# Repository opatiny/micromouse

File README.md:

# Algernon: A custom micromouse robot

YouTube demo of the project: https://youtu.be/nz4QlaSIkbY

Main repository for my bachelor's thesis project.

## Related repositories

The software fo this robot can be found in the two following repositories:

- Software for the microcontroller: [opatiny/ms-software](https://github.com/opatiny/ms-software)
- TypeScript code for the debug web page (is then built and uploaded on the MCU): [opatiny/ms-webpage](https://github.com/opatiny/ms-webpage)

## Abstract

This project was inspired by the micromouse competitions, in which small autonomous maze-solving robots compete to solve an unknown maze in the shortest possible time. The main focus of the project was to design a micromouse from scratch, which implied electrical and mechanical design, as well as the manufacturing of our own custom PCB. A physical prototype of the robot was fully assembled and tested. The robot implements 5 ToF distance sensors, an accelerometer and two brushed DC motors with encoders. The microcontroller is an ESP32-S3, and a 2P1S LiPo battery is used as a power supply. On the software side, all of the sensors were tested independently and are functional. A basic odometry task was also implemented, which allows to track the robot's position, and speed regulation of the wheels was added. What is more, a remote debug interface using WiFi was programmed in order to visualize the robot's status in real time.

## Report of the project

The report of this thesis can be found in the `docs` folder of this repository: [bachelor-thesis-opatiny.pdf](./docs/bachelor-thesis-opatiny.pdf)

## Repository structure

These are the main folders in this repository:

- `docs`: All sorts of documentation about the project, as well as the datasheets and useful images of the components used.
- `electronics`: Contains all the KiCad files of the PCB.
- `mechanics`: All files related to mechanical design and manufacturing. Also contains all of our custom maze files.
- `matlab`: Calculations and plot realized during the project.
- `software`: Not the actual micro-controller software. This only contains a few tests done using the Micromouse Simulator tool.

## Software

All the software of the robot is in its own repository: [opatiny/ms-software](https://github.com/opatiny/micromouse).

## Electronic design

The robot's PCB was fully designed in KiCad. The list of all the components used can be found in [docs/electronics/mouseHardware.md](./docs/electronics/mouseHardware.md).

Render of the final PCB

3D view of the completed robot

## Mechanical design

The mechanical design is relatively simple since the PCB is the main structural element. We just had to design our own caster wheel, that are 3D printed out of PETG, and custom bumpers, 3D printed out of flexible filament.

Comparison of commercial and custom caster wheel

Close-up of the bumper

## Custom maze

In order to test our robot, we designed our own maze. The walls are 3mm MDF, spray painted white. The connectors are 3D printed out of PETG. Additional "bridge" parts are use to ensure the walls are parallel, and at the right distance from each other. All the parts were designed in solidworks.

The four types of connectors

Example of a small section of maze, integrating one of the "bridge" parts

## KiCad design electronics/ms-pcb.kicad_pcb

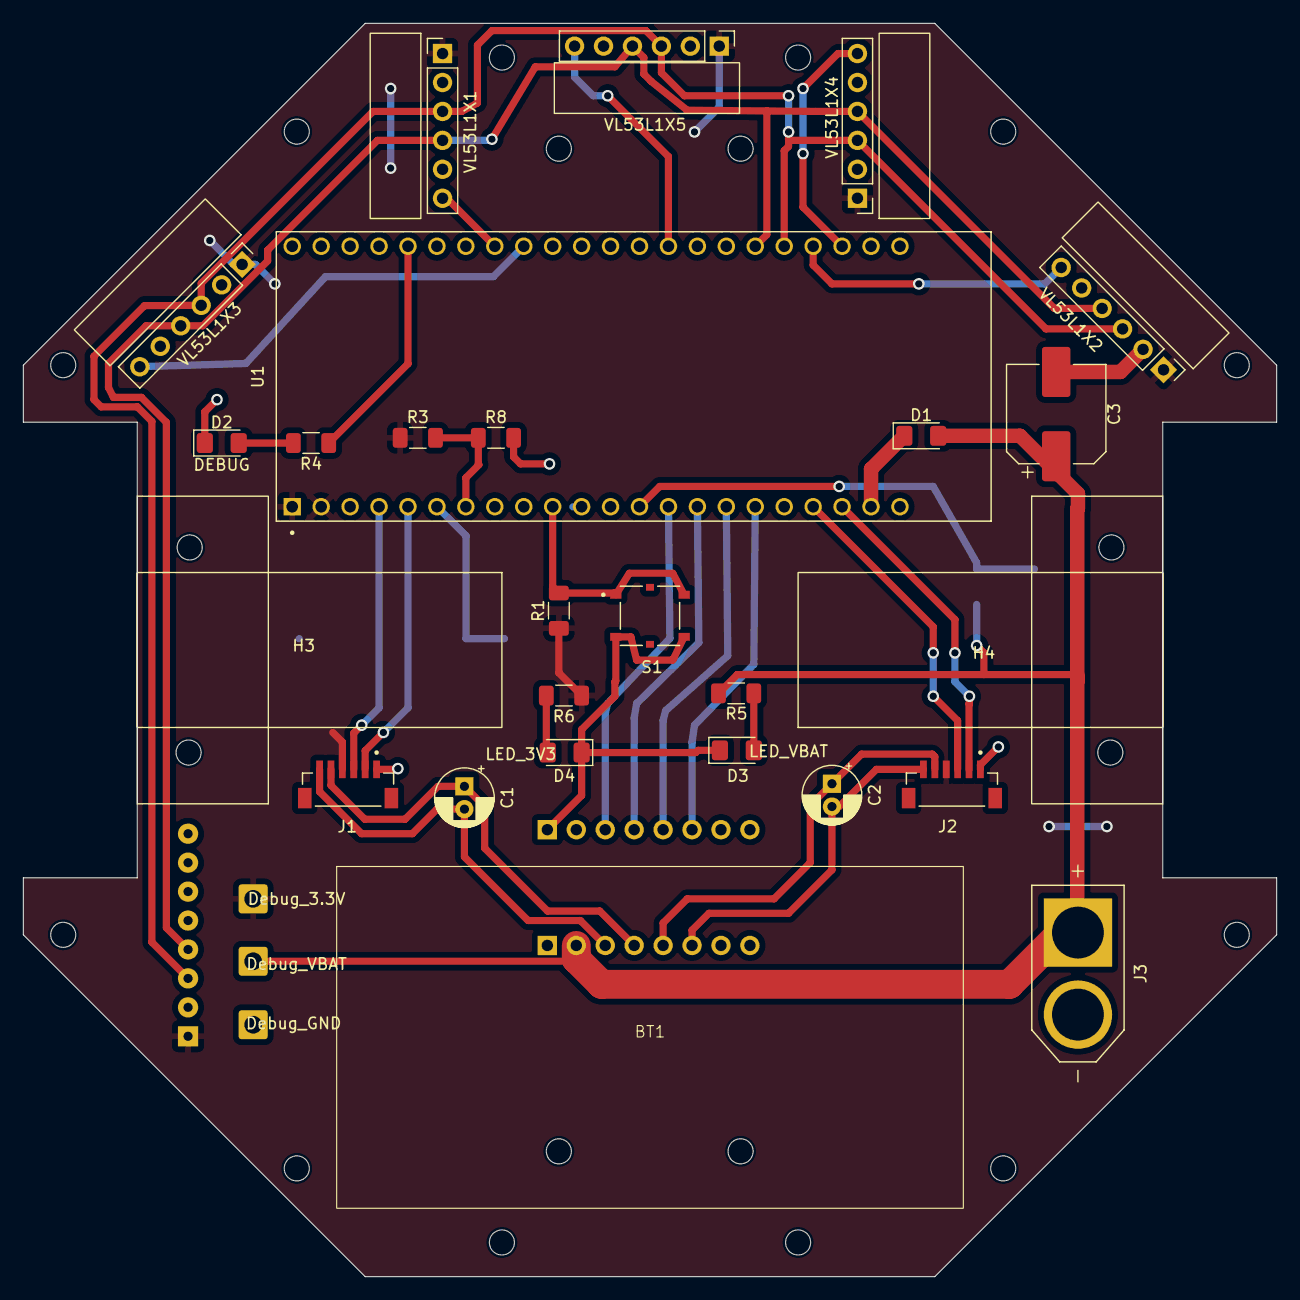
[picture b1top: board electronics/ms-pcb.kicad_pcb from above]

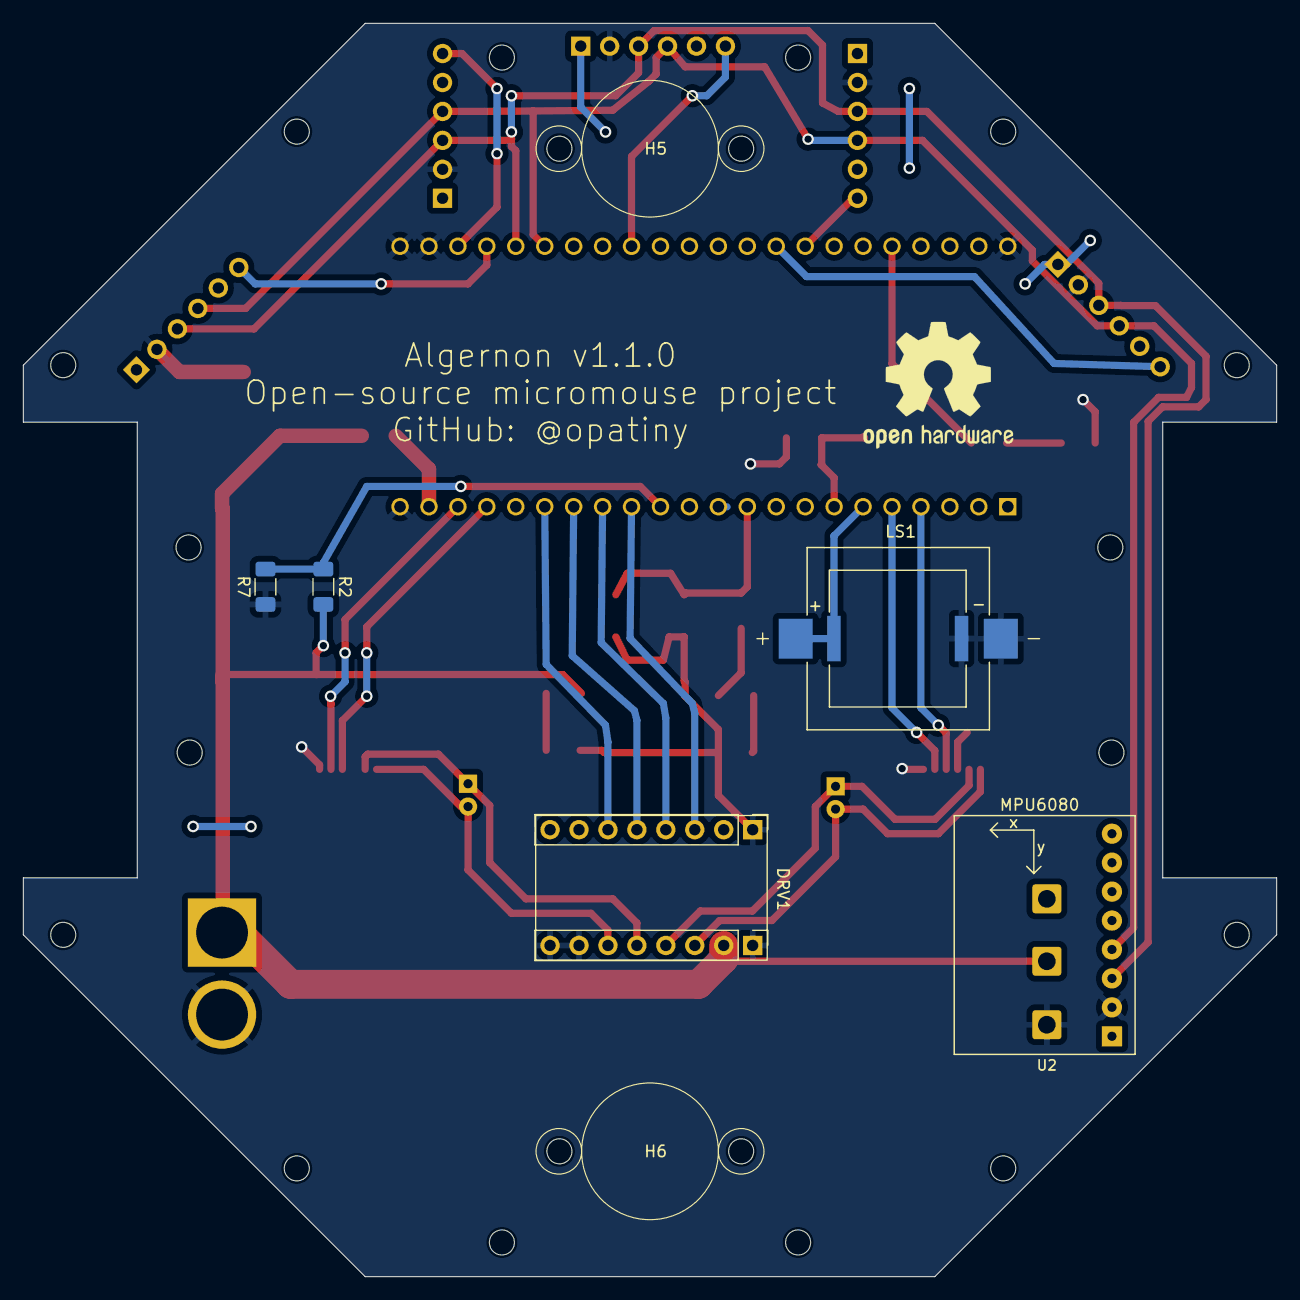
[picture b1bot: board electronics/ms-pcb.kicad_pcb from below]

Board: 2 copper layers, 110.0 x 110.0 mm, 38 parts (7 on the bottom side), 31 nets.

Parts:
BT1: Battery; LiPo_2S1P_Battery
C1, C2: 0.1uF; CP_Radial_D5.0mm_P2.00mm
C3: 220uF; CP_Elec_8x10.5
D1: D_Schottky; D_1206_3216Metric_Pad1.42x1.75mm_HandSolder
D2: DEBUG; LED_1206_3216Metric_Pad1.42x1.75mm_HandSolder
D3: LED_VBAT; LED_1206_3216Metric_Pad1.42x1.75mm_HandSolder
D4: LED_3V3; LED_1206_3216Metric_Pad1.42x1.75mm_HandSolder
DRV1: DRV8833; Polulu_DRV8833
H1: Bumper_front; Micromouse_bumper
H2: Bumper_back; Micromouse_bumper
H3, H4: Motor_holes; Polulu_Micro_Gearmotor
H5, H6: Caster_wheel; caster_wheel_custom
H7: Debug_3.3V; SolderWire-0.75sqmm_1x01_D1.25mm_OD2.3mm
H8: Debug_VBAT; SolderWire-0.75sqmm_1x01_D1.25mm_OD2.3mm
H9: Debug_GND; SolderWire-0.75sqmm_1x01_D1.25mm_OD2.3mm
J1: Left motor; JST_SH_6pins
J2: Right motor; JST_SH_6pins
J3: XT60-M; AMASS_XT60-M
LS1: PKLCS1212E20A0-R1; buzzer_double_footprint
R1: 20k; R_1206_3216Metric_Pad1.30x1.75mm_HandSolder
R2, R3, R4: 10k; R_1206_3216Metric_Pad1.30x1.75mm_HandSolder
R5: 40k; R_1206_3216Metric_Pad1.30x1.75mm_HandSolder
R6: 5k; R_1206_3216Metric_Pad1.30x1.75mm_HandSolder
R7, R8: 1k; R_1206_3216Metric_Pad1.30x1.75mm_HandSolder
S1: PTS526_SMG15_SMTR2_LFS; SW_PTS526_SMG15_SMTR2_LFS
U1: ESP32-S3-DEVKITC-1U-N8R2; XCVR_ESP32-S3-DEVKITC-1U-N8R2
U2: GY-521
VL53L1X1: Left; TinyTronics_VL53L1X
VL53L1X2: Front-right; TinyTronics_VL53L1X
VL53L1X3: Front-left; TinyTronics_VL53L1X
VL53L1X4: Right; TinyTronics_VL53L1X
VL53L1X5: Front; TinyTronics_VL53L1X_header_front

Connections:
+3.3V: H7.1, J1.4 (VCC), J2.4 (VCC), R1.1, R3.1, R6.1, U1.J1_1 (3V3), U1.J1_2 (3V3), U2.VCC, VL53L1X1.1 (VIN), VL53L1X2.1 (VIN), VL53L1X3.1 (VIN), VL53L1X4.1 (VIN), VL53L1X5.1 (VIN)
+BATT: C3.1, D1.2 (A), DRV1.10 (VIN), H8.1, J3.P (POS), R2.1, R5.1
DEBUG: R4.1, U1.J3_5 (GPIO2)
DRV_L1: DRV1.3 (BIN1), U1.J1_14 (GPIO46)
DRV_L2: DRV1.4 (BIN2), U1.J1_15 (GPIO9)
DRV_R1: DRV1.6 (AIN1), U1.J1_17 (GPIO11)
DRV_R2: DRV1.5 (AIN2), U1.J1_16 (GPIO10)
ENC_L1: J1.3 (OUT_A), U1.J1_4 (GPIO4)
ENC_L2: J1.2 (OUT_B), U1.J1_5 (GPIO5)
ENC_R1: J2.3 (OUT_A), U1.J1_19 (GPIO13)
ENC_R2: J2.2 (OUT_B), U1.J1_20 (GPIO14)
GND: C3.2, D2.1 (K), D3.1 (K), D4.1 (K), DRV1.1 (GND), DRV1.9 (GND), DRV1.15 (AISEN), DRV1.16 (BISEN), H9.1, J1.1 (GND), J2.1 (GND), J3.N (NEG), LS1.N, R7.2, R8.2, S1.3, S1.4, U1.J1_22 (GND), U1.J3_1 (GND), U1.J3_21 (GND), U1.J3_22 (GND), U2.GND, VL53L1X1.2 (GND), VL53L1X2.2 (GND), VL53L1X3.2 (GND), VL53L1X4.2 (GND), VL53L1X5.2 (GND)
MOT_L1: C1.2, DRV1.11 (BOUT1), J1.6 (M1)
MOT_L2: C1.1, DRV1.12 (BOUT2), J1.5 (M2)
MOT_R1: C2.2, DRV1.14 (AOUT1), J2.6 (M1)
MOT_R2: C2.1, DRV1.13 (AOUT2), J2.5 (M2)
Mes_VCC: R3.2, R8.1, U1.J1_7 (GPIO7)
Mes_bat: R2.2, R7.1, U1.J1_13 (GPIO3)
unnamed: D1.1 (K), U1.J1_21 (5V0)
unnamed: D2.2 (A), R4.2
unnamed: D3.2 (A), R5.2
unnamed: D4.2 (A), R6.2
SCL: U1.J3_18 (GPIO21), U2.SCL, VL53L1X1.3 (SCL), VL53L1X2.3 (SCL), VL53L1X3.3 (SCL), VL53L1X4.3 (SCL), VL53L1X5.3 (SCL)
SDA: U1.J3_17 (GPIO47), U2.SDA, VL53L1X1.4 (SDA), VL53L1X2.4 (SDA), VL53L1X3.4 (SDA), VL53L1X4.4 (SDA), VL53L1X5.4 (SDA)
XSHUT_F: U1.J3_14 (GPIO0), VL53L1X5.6 (XSHUT)
XSHUT_FL: U1.J3_9 (MTCK/GPIO39), VL53L1X3.6 (XSHUT)
XSHUT_FR: U1.J3_19 (USB_D+/GPIO20), VL53L1X2.6 (XSHUT)
XSHUT_L: U1.J3_8 (MTDO/GPIO40), VL53L1X1.6 (XSHUT)
XSHUT_R: U1.J3_20 (USB_D-/GPIO19), VL53L1X4.6 (XSHUT)
button: R1.2, S1.1, S1.2, U1.J1_10 (GPIO17)
buzzer: LS1.P, U1.J1_6 (GPIO6)

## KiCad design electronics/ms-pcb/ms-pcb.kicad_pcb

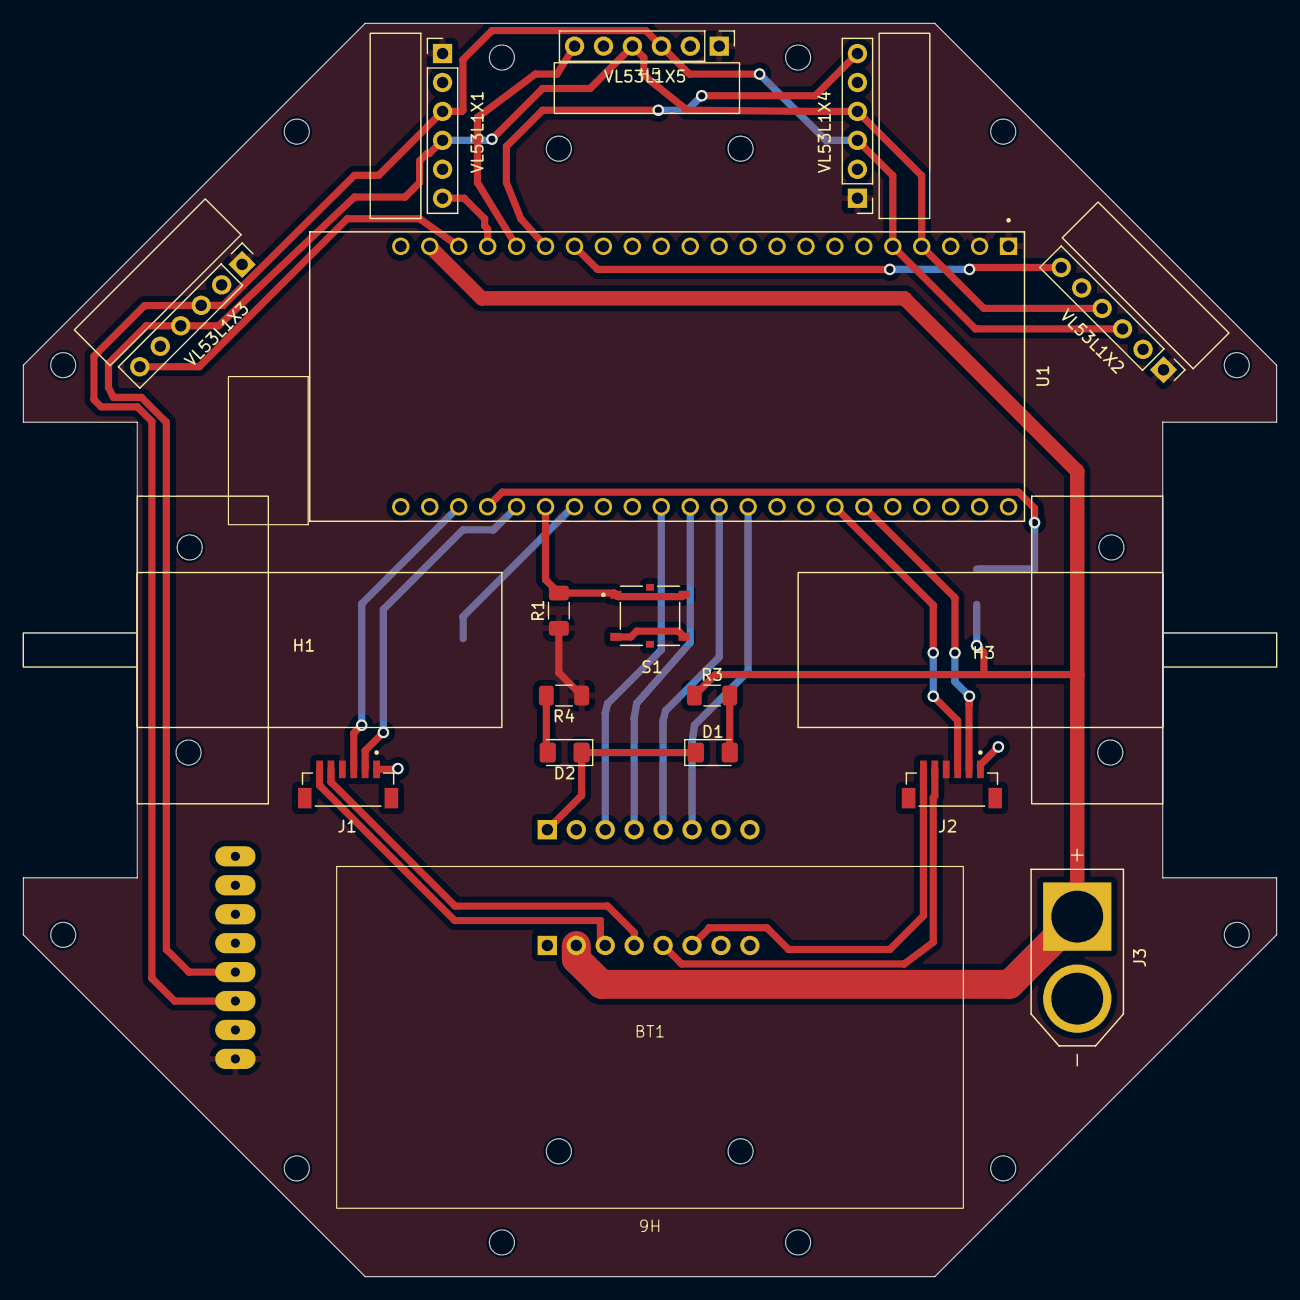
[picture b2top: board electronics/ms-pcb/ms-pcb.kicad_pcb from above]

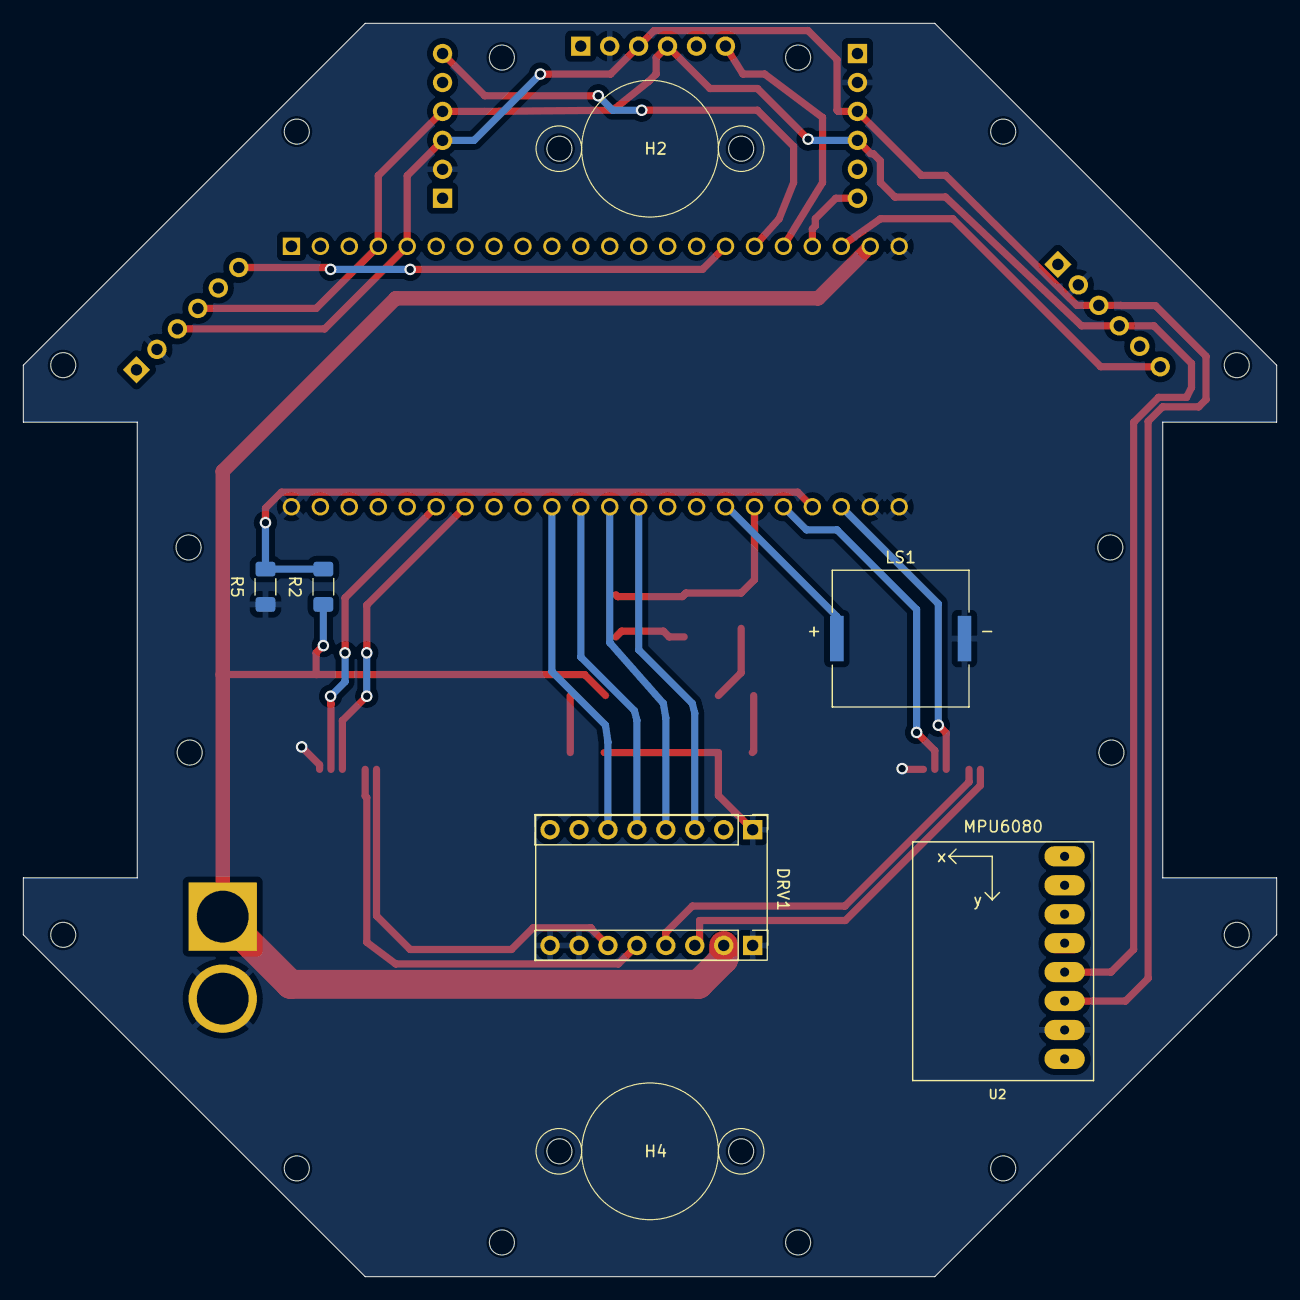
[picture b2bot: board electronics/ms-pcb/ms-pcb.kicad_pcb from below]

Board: 2 copper layers, 110.0 x 110.0 mm, 27 parts (7 on the bottom side), 28 nets.

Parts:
BT1: Battery; LiPo_2S1P_Battery
D1: LED_VBAT; LED_1206_3216Metric_Pad1.42x1.75mm_HandSolder
D2: LED_3V3; LED_1206_3216Metric_Pad1.42x1.75mm_HandSolder
DRV1: DRV8833; Polulu_DRV8833
H1, H3: Motor_holes; Polulu_Micro_Gearmotor
H2, H4: Caster_wheel_holes; caster_wheel_custom
H5: Bumper_front; Micromouse_bumper
H6: Bumper_back; Micromouse_bumper
J1: Left motor; JST_SH_6pins
J2: Right motor; JST_SH_6pins
J3: XT60-M; AMASS_XT60-M
LS1: PKLCS1212E20A0-R1; SPKR_PKLCS1212E20A0-R1
R1: 20k; R_1206_3216Metric_Pad1.30x1.75mm_HandSolder
R2: 10k; R_1206_3216Metric_Pad1.30x1.75mm_HandSolder
R3, R4: 220; R_1206_3216Metric_Pad1.30x1.75mm_HandSolder
R5: 1k; R_1206_3216Metric_Pad1.30x1.75mm_HandSolder
S1: PTS526_SMG15_SMTR2_LFS; SW_PTS526_SMG15_SMTR2_LFS
U1: ESP32-S3-DEVKITC-1U-N8R2; XCVR_ESP32-S3-DEVKITC-1U-N8R2
U2: GY-521
VL53L1X1: Left; TinyTronics_VL53L1X
VL53L1X2: Front-right; TinyTronics_VL53L1X
VL53L1X3: Front-left; TinyTronics_VL53L1X
VL53L1X4: Right; TinyTronics_VL53L1X
VL53L1X5: Front; TinyTronics_VL53L1X_header_front

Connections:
+3.3V: J1.4 (VCC), J2.4 (VCC), R1.1, R4.1, U1.J1_1 (3V3), U1.J1_2 (3V3), U2.VCC, VL53L1X1.1 (VIN), VL53L1X2.1 (VIN), VL53L1X3.1 (VIN), VL53L1X4.1 (VIN), VL53L1X5.1 (VIN)
+BATT: DRV1.10 (VIN), J3.P (POS), R2.1, R3.1, U1.J1_21 (5V0)
DRV_L1: DRV1.3 (BIN1), U1.J3_13 (GPIO35)
DRV_L2: DRV1.4 (BIN2), U1.J3_12 (GPIO36)
DRV_R1: DRV1.6 (AIN1), U1.J3_10 (GPIO38)
DRV_R2: DRV1.5 (AIN2), U1.J3_11 (GPIO37)
ENC_L1: J1.3 (OUT_A), U1.J3_20 (USB_D-/GPIO19)
ENC_L2: J1.2 (OUT_B), U1.J3_18 (GPIO21)
ENC_R1: J2.3 (OUT_A), U1.J3_7 (MTDI/GPIO41)
ENC_R2: J2.2 (OUT_B), U1.J3_6 (MTMS/GPIO42)
GND: D1.1 (K), D2.1 (K), DRV1.1 (GND), DRV1.9 (GND), DRV1.15 (AISEN), DRV1.16 (BISEN), J1.1 (GND), J2.1 (GND), J3.N (NEG), LS1.N, R5.2, S1.3, S1.4, U1.J1_22 (GND), U1.J3_1 (GND), U1.J3_21 (GND), U1.J3_22 (GND), U2.GND, VL53L1X1.2 (GND), VL53L1X2.2 (GND), VL53L1X3.2 (GND), VL53L1X4.2 (GND), VL53L1X5.2 (GND)
MOT_L1: DRV1.11 (BOUT1), J1.6 (M1)
MOT_L2: DRV1.12 (BOUT2), J1.5 (M2)
MOT_R1: DRV1.14 (AOUT1), J2.6 (M1)
MOT_R2: DRV1.13 (AOUT2), J2.5 (M2)
unnamed: D1.2 (A), R3.2
unnamed: D2.2 (A), R4.2
unnamed: S1.G1, S1.G2
SCL: U1.J1_5 (GPIO5), U2.SCL, VL53L1X1.3 (SCL), VL53L1X2.3 (SCL), VL53L1X3.3 (SCL), VL53L1X4.3 (SCL), VL53L1X5.3 (SCL)
SDA: U1.J1_4 (GPIO4), U2.SDA, VL53L1X1.4 (SDA), VL53L1X2.4 (SDA), VL53L1X3.4 (SDA), VL53L1X4.4 (SDA), VL53L1X5.4 (SDA)
Vmes: R2.2, R5.1, U1.J3_19 (USB_D+/GPIO20)
XSHUT_F: U1.J1_18 (GPIO12), VL53L1X5.6 (XSHUT)
XSHUT_FL: U1.J1_20 (GPIO14), VL53L1X3.6 (XSHUT)
XSHUT_FR: U1.J1_16 (GPIO10), VL53L1X2.6 (XSHUT)
XSHUT_L: U1.J1_19 (GPIO13), VL53L1X1.6 (XSHUT)
XSHUT_R: U1.J1_17 (GPIO11), VL53L1X4.6 (XSHUT)
button: R1.2, S1.1, S1.2, U1.J3_17 (GPIO47)
buzzer: LS1.P, U1.J3_16 (GPIO48)

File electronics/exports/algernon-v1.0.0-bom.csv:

"Reference",	"Value",	"Datasheet",	"Footprint",	"Qty",	"DNP"
"BT1",	"Battery",	"~",	"footprints:LiPo_2S1P_Battery",	"1",	""
"D1",	"LED_VBAT",	"~",	"LED_SMD:LED_1206_3216Metric_Pad1.42x1.75mm_HandSolder",	"1",	""
"D2",	"LED_3V3",	"~",	"LED_SMD:LED_1206_3216Metric_Pad1.42x1.75mm_HandSolder",	"1",	""
"DRV1",	"DRV8833",	"",	"footprints:Polulu_DRV8833",	"1",	""
"H1,H4",	"Motor_holes",	"~",	"footprints:Polulu_Micro_Gearmotor",	"2",	""
"H2,H5",	"Caster_wheel_holes",	"~",	"footprints:caster_wheel_custom",	"2",	""
"H3",	"Bumper_front",	"~",	"footprints:Micromouse_bumper",	"1",	""
"H6",	"Bumper_back",	"~",	"footprints:Micromouse_bumper",	"1",	""
"J1",	"Left motor",	"",	"footprints:JST_SH_6pins",	"1",	""
"J2",	"Right motor",	"",	"footprints:JST_SH_6pins",	"1",	""
"J3",	"XT60-M",	"",	"footprints:AMASS_XT60-M",	"1",	""
"LS1",	"PKLCS1212E20A0-R1",	"",	"footprints:buzzer_double_footprint",	"1",	""
"R1",	"20k",	"~",	"Resistor_SMD:R_1206_3216Metric_Pad1.30x1.75mm_HandSolder",	"1",	""
"R2",	"10k",	"~",	"Resistor_SMD:R_1206_3216Metric_Pad1.30x1.75mm_HandSolder",	"1",	""
"R3,R4",	"220",	"~",	"Resistor_SMD:R_1206_3216Metric_Pad1.30x1.75mm_HandSolder",	"2",	""
"R5",	"1k",	"~",	"Resistor_SMD:R_1206_3216Metric_Pad1.30x1.75mm_HandSolder",	"1",	""
"S1",	"PTS526_SMG15_SMTR2_LFS",	"",	"footprints:SW_PTS526_SMG15_SMTR2_LFS",	"1",	""
"U1",	"ESP32-S3-DEVKITC-1U-N8R2",	"",	"footprints:XCVR_ESP32-S3-DEVKITC-1U-N8R2",	"1",	""
"U2",	"GY-521",	"",	"footprints:GY-521",	"1",	""
"VL53L1X1",	"Left",	"",	"footprints:TinyTronics_VL53L1X",	"1",	""
"VL53L1X2",	"Front-right",	"",	"footprints:TinyTronics_VL53L1X",	"1",	""
"VL53L1X3",	"Front-left",	"",	"footprints:TinyTronics_VL53L1X",	"1",	""
"VL53L1X4",	"Right",	"",	"footprints:TinyTronics_VL53L1X",	"1",	""
"VL53L1X5",	"Front",	"",	"footprints:TinyTronics_VL53L1X_header_front",	"1",	""

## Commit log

2023-10-08 docs: create readme
2023-10-08 sw: first maze model
2023-10-13 sw: add studs to corners
2023-10-13 sw: working on maze corners
2023-10-15 sw: enhance wall
2023-12-28 sw: adapt corner play
2023-12-28 sw: design spacer
2023-12-28 sw: spacer v2
2023-12-28 refactor: move slicer files to manufacturing folder
2023-12-31 refactor: rename slicer to prusaSlicer
2023-12-31 lb: add lignburn files
2023-12-31 sw: enhancing maze spacer
2023-12-31 sw: export 4 units wall
2024-01-01 chore: cleanup useless gcode
2024-01-20 manuf: working on corners
2024-01-20 matlab: small motors calculation
2024-02-14 docs: add some datasheets
2024-02-19 matlab: work on motors script
2024-02-19 docs: motors doc
2024-02-20 docs: motors and batteries
2024-02-20 matlab: enhance motors script
2024-02-21 docs: working on motors and electronics choice
2024-02-22 docs: look for suitable motor
2024-02-23 docs: start sensors doc
2024-02-26 docs: enhance regulation docs
2024-02-28 docs: continue state of the art
2024-02-28 docs: start more software doc
2024-02-29 soft: start playing with mms
2024-02-29 mms: start Maze handling
2024-02-29 docs: start lab notebook
2024-02-29 mms: initMaze works
2024-02-29 mms: small bug with maze pointers
2024-03-01 mms: maze sensing works
2024-03-03 docs: add datasheets
2024-03-04 mms: try to debug updateCellWalls
2024-03-10 docs: enhance list of stuff to buy
2024-03-14 feat: script to change I2C dist sensor address
2024-03-14 docs: IO expander
2024-03-18 chore: add gitignore
2024-03-18 docs: looking for good battery
2024-03-19 docs: buy batteries and charger
2024-03-19 docs: looking for IO expander
2024-03-19 docs: enhance lab notebook
2024-03-20 mec: add drv8833 3d model
2024-03-21 docs: add esp pins attribution md
2024-03-21 refactor: move files to state of the art folder
2024-03-22 chore: create outdated folder
2024-03-22 docs: add MCU doc file
2024-03-25 docs: enhance distance sensors doc
2024-03-26 docs: motors and batteries doc
2024-03-27 docs: start mouse hardware md
2024-03-27 elec: add components ecad files and start PCB v0.1
2024-03-27 refactor: delete solidworks folder
2024-03-27 docs: espressif esp32 pin mapping
2024-03-27 docs: finish pin mapping espressif
2024-03-27 elec: first PCB schematic draft
2024-04-03 docs: find dimensions of some components
2024-04-03 elec: design some missing footprints
2024-04-03 elec: start PCB layout
2024-04-04 elec: minor schematic fixes
2024-04-05 matlab: analyse battery voltage
2024-04-08 docs: update lab notebook
2024-04-08 docs: working on encoders
2024-04-09 elec: add more 3D and link them to footprints
2024-04-09 elec: add most 3D models
    Closes: #19
2024-04-10 mec: add some step files
2024-04-10 mec: start solidworks design
2024-04-10 elec: add more 3D models and enhance layout
2024-04-10 mec: prusa slicer files
2024-04-10 mec: design custom caster wheel, bumper and pcb base
2024-04-10 elec: enhance PCB v0.1 layout
2024-04-10 docs: lab notebook
2024-04-12 mec: enhance bumper
2024-04-12 elec: PCB layout wiring
2024-04-12 refactor: move manufacturing folder
2024-04-12 docs: redo pin mapping
2024-04-12 refactor: remove useless folder ms-pcb
2024-04-12 chore: update gitignore
2024-04-15 elec: minor PCB layout changes
2024-04-16 fix: finish PCB layout v1.0.0
    Closes: #10
2024-04-16 docs: cleanup datasheets
2024-04-17 refactor: move mouseHardware.md
2024-04-17 fix: caster wheel
    Closes: #34
2024-04-17 matlab: battery script
2024-04-17 mec: design bumper springy
2024-04-18 matlab: working on distance sensors calbration
2024-04-18 matlab: calibration of distance sensors
2024-04-19 matlab: encoders script
2024-04-24 elec: export schematic of pcb v1.0.0 as pdf
2024-04-24 docs: reformat data readme
2024-04-26 matlab: encoders data script
2024-04-29 elec: change debug leds resistors values
2024-05-02 docs: add espressif MCU datasheet
2024-05-03 elec: start PCB v1.1.0
2024-05-03 elec: PCB v1.1.0 finished
    Still need last checks before ordering.
2024-05-03 docs: lab notes of the week
2024-05-06 mec: final prusa slicer files for bumper and caster wheel
2024-05-06 elec: final check for PCB v1.1.0
    Refs: #51
2024-05-06 docs: edit to buy list
2024-05-14 elec: minor changes in PCB
2024-05-15 docs: start code structure md
2024-05-17 docs: fix v1.1.0 pin mapping
2024-05-24 matlab: script to visualice speed rpm vs command
2024-05-27 elec: fix vcc voltage measurement pin
    Closes: #66
2024-05-28 matlab: working on speed calibration
2024-05-28 matlab: speed calibration
2024-05-29 matlab: parabola fit works for speed calibration
2024-05-29 matalb: function for speed to command works
2024-05-29 matlab: still working on speed calibration
2024-06-06 matlab: cpp and matlab correspond for speed calibration
2024-06-07 matlab: calibration test
2024-06-07 matlab: minor changes
2024-06-12 matlab: script to test pid
2024-06-14 matlab: test PID results
2024-06-14 docs: more common errors
2024-06-17 docs: lab notebook current situation
2024-06-17 matlab: new speed measurement
2024-06-19 matlab: controller delay impact
2024-06-21 matlab: test low pass filter for PID derivative
2024-06-28 pcb: add mouse center point
2024-06-28 docs: new error doc
2024-07-03 minor changes
2024-07-05 docs: minor changes
2024-07-24 add licence
2024-07-24 docs: lab notebook for july
2024-07-24 docs: schottky diode datasheet
2024-07-30 matlab: rework wheel speed plots
2024-07-30 docs: fill readme
2024-07-30 docs: fix typos in readme
2024-08-06 matlab: compare high and low speeds
2024-08-07 matlab: measure robot max accel
2024-08-12 matlab: compute robot's max acceleration
2024-08-14 docs: add repos links
2024-08-16 docs: add pdf of report
2024-08-16 elec: add comments to PCB
2024-08-19 docs: update thesis pdf
2024-08-31 docs: update README.md
2024-09-09 docs: small changes
